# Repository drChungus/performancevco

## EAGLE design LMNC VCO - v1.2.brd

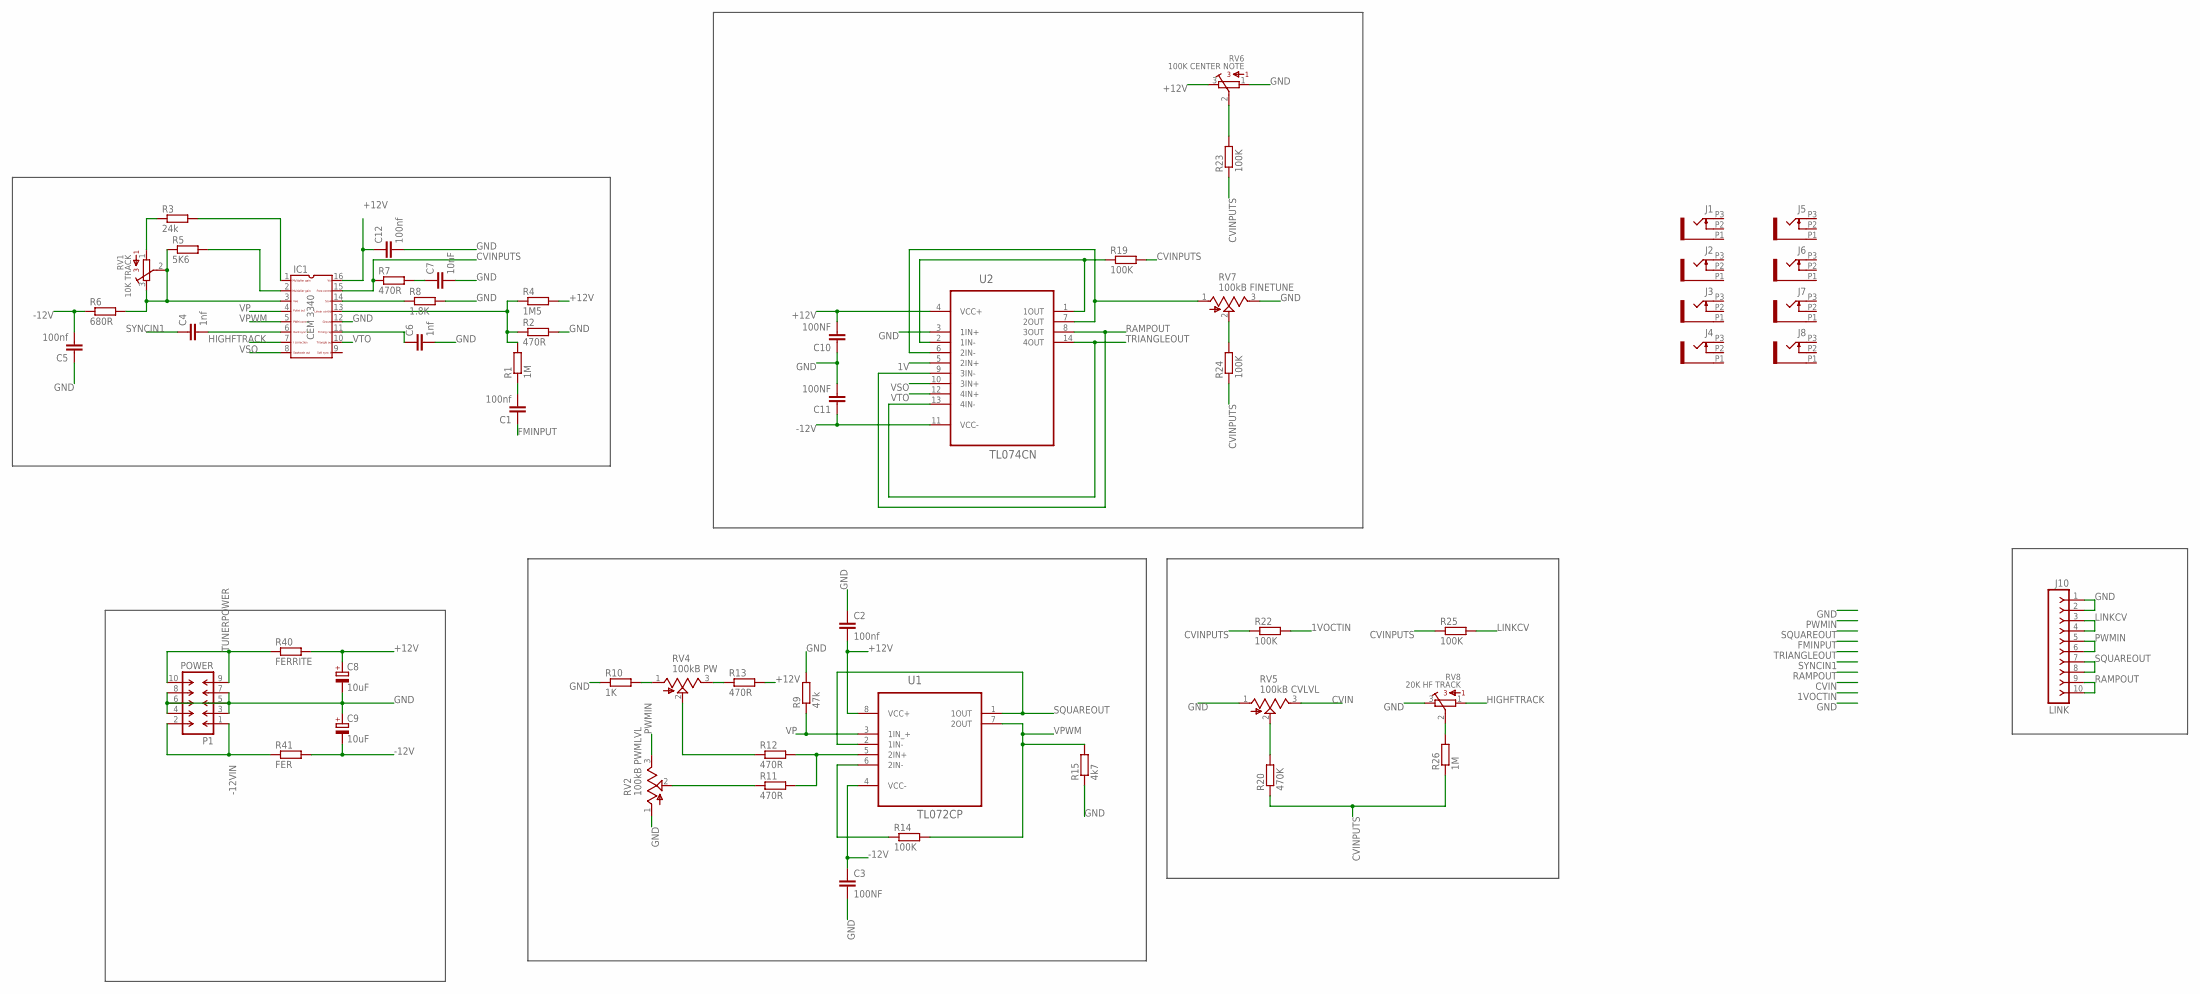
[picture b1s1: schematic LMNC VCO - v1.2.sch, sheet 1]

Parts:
C1, C2, C5, C12: 100nf; C0603
C3, C10, C11: 100NF; C0603
C4, C6: 1nf; C0603
C7: 10nF; C0603
C8, C9: 10uF; 153CLV-0605
IC1: CEM3340; DIL16
J1, J2, J3, J4, J5, J6, J7, J8: PJ301_THONKICONNTME; WQP_PJ_301M_TME
J10: LINK; SIP-100-10-32Y
P1: POWER; DIL-100-2X05
R1, R26: 1M; R0603
R2, R7, R11, R12, R13: 470R; R0603
R3: 24k; R0603
R4: 1M5; R0603
R5: 5K6; R0603
R6: 680R; R0603
R8: 1.8K; R0603
R9: 47k; R0603
R10: 1K; R0603
R14, R19, R22, R23, R24, R25: 100K; R0603
R15: 4k7; R0603
R20: 470K; R0603
R40: FERRITE; R0603
R41: FER; R0603
RV1: 10K TRACK; 3386W
RV2: 100kB PWMLVL; ALPS_POT_VERTICAL
RV4: 100kB PW; ALPS_POT_VERTICAL
RV5: 100kB CVLVL; ALPS_POT_VERTICAL
RV6: 100K CENTER NOTE; 3386W
RV7: 100kB FINETUNE; ALPS_POT_VERTICAL
RV8: 20K HF TRACK; 3386W
U1: TL072CP; DIP254P762X508-8
U2: TL074CN; DIP254P762X508-14

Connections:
1V: U2.5 (2IN+)
1VOCTIN: R22.2
+12V: C2.2, C8.+, C10.2, C12.1, IC1.16, R4.2, R13.2, R40.2, RV6.3, U1.8 (VCC+), U2.4 (VCC+)
-12V: C3.1, C5.2, C9.-, C11.1, R6.1, R41.2, U1.4 (VCC-), U2.11 (VCC-)
-12VIN: P1.1, P1.2, R41.1
CVIN: RV5.3 (B)
CVINPUTS: IC1.15, R7.1, R19.2, R20.1, R22.1, R23.1, R24.1, R25.1, R26.1
FMINPUT: C1.1
GND: C2.1, C3.2, C5.1, C6.2, C7.2, C8.-, C9.+, C10.1, C11.2, C12.2, IC1.12, J10.1, J10.2, P1.3, P1.4, P1.5, P1.6, P1.7, P1.8, R2.2, R8.2, R9.2, R10.1, R15.1, RV2.1 (A), RV5.1 (A), RV6.1, RV7.3 (B), RV8.3, U2.3 (1IN+)
HIGHFTRACK: IC1.7, RV8.1
LINKCV: J10.3, J10.4, R25.2
unnamed: IC1.2, R5.2
unnamed: IC1.1, R3.2
unnamed: IC1.3, R5.1, R6.2, RV1.2, RV1.3
unnamed: R3.1, RV1.1
unnamed: C7.1, R7.2
unnamed: C1.2, R1.1
unnamed: C4.2, IC1.6
unnamed: C6.1, IC1.11
unnamed: R14.1, U1.6 (2IN-)
unnamed: R11.2, R12.2, U1.5 (2IN+)
unnamed: IC1.14, R8.1
unnamed: IC1.13, R1.2, R2.1, R4.1
unnamed: R12.1, RV4.2 (W)
unnamed: R11.1, RV2.2 (W)
unnamed: R10.2, RV4.1 (A)
unnamed: R13.1, RV4.3 (B)
unnamed: RV7.1 (A), U2.6 (2IN-), U2.7 (2OUT)
unnamed: R24.2, RV7.2 (W)
unnamed: R19.1, U2.1 (1OUT), U2.2 (1IN-)
unnamed: R23.2, RV6.2
unnamed: R20.2, RV5.2 (W)
unnamed: R26.2, RV8.2
PWMIN: J10.5, J10.6, RV2.3 (B)
RAMPOUT: J10.9, J10.10, U2.8 (3OUT), U2.9 (3IN-)
SQUAREOUT: J10.7, J10.8, U1.1 (1OUT), U1.2 (1IN-)
SYNCIN1: C4.1
TRIANGLEOUT: U2.13 (4IN-), U2.14 (4OUT)
TUNERPOWER: P1.9, P1.10, R40.1
VP: IC1.4, R9.1, U1.3 (1IN_+)
VPWM: IC1.5, R14.2, R15.2, U1.7 (2OUT)
VSO: IC1.8, U2.10 (3IN+)
VTO: IC1.10, U2.12 (4IN+)

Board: 2 copper layers, 57 parts (15 on the bottom side), 38 nets, no tracks yet.

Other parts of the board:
U$1: EURO_PCB_6HP

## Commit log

2021-08-05 Update1
    Removed Tuner Arduino,
    Replaced Caps to SMD footprint
2021-08-05 SMD-ification
    and removed V reference and switch
2021-08-05 Started Layout
2021-08-06 Started two layered pcb design

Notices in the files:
parts and their libraries:
con-headers-jp: Copyright (C) 2008, Bob Starr
